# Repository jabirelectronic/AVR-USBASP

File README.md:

# USBasp - USB programmer for Atmel AVR controllers
The above programmer is from the website https://www.fischl.de/usbasp/
Modeled and redesigned.
There are some tips about this design:
Internal and external voltage separator section is considered.
A logic 5V output is provided.
A 3.3V output is also provided for low power micros.
And a 500 mA fuse is placed in this circuit to prevent short circuit and damage to the usb port.
The board is designed in two layers.
Be sure to use version 7 of kicad software to view the schematic and PCB map.

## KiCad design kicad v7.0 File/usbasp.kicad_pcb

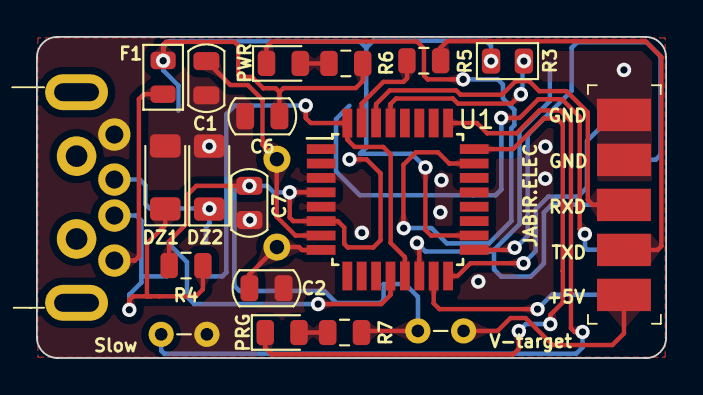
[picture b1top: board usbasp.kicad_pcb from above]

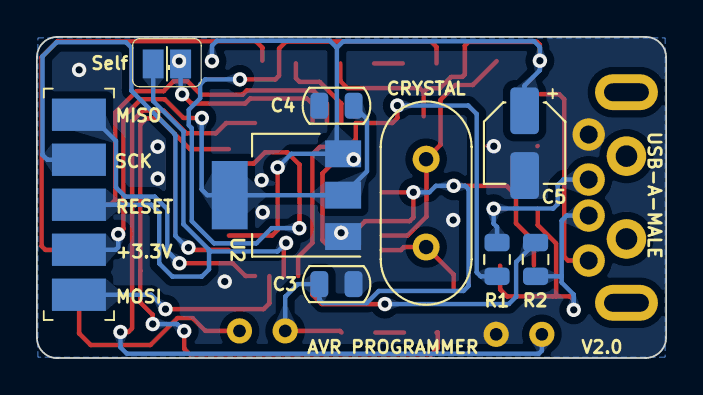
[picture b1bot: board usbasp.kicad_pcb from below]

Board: 2 copper layers, 35.0 x 17.8 mm, 28 parts (9 on the bottom side), 24 nets.

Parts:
+5V: B5B-XH-A_LF__SN_; PinHeader_1x5_P2.5mm_Drill1.1mm
C1, C2, C3, C4, C6, C7: 100nF_0603_16V; C_0805_2012Metric
C5: CP_Radial_D8.0mm_P5.00mm 4.7; CP_Elec_4x5.4
CRYSTAL: 16MHz_18pF_FA238; Crystal_HC49-U_Vertical
DZ1, DZ2: D3Z6V2BF; D_MiniMELF
F1: Fuse; Fuse_0805_2012Metric
MISO: B5B-XH-A_LF__SN_; PinHeader_1x5_P2.5mm_Drill1.1mm
PRG: LED; LED_0805_2012Metric
PWR: LED; LED_0805_2012Metric
R1, R2, R4, R5, R6, R7: 0R_0603; R_0805_2012Metric
R3: 110k_0603; R_0805_2012Metric
Self: Jumper_2_Bridged; JUMPER_SMD_1x2
Slow: Jumper_2_Bridged; Jumper_P2.54mm_D0.7mm
U1: ATmega8A-A; TQFP-32_7x7mm_P0.8mm
U2: AMS1117; SOT-223-3_TabPin2
USB-A-MALE: USB_A; USB_Male_A_UP2-AH-1-TH
V-target: Jumper_2_Bridged; Jumper_P2.54mm_D0.7mm

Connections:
Earth: +5V.4, +5V.5, C1.1, C2.1, C3.2, C4.1, C5.2, C6.2, C7.2, DZ1.2 (A), DZ2.2 (A), Slow.2 (B), U1.3 (GND), U1.5 (GND), U1.21 (AGND), U2.1 (ADJ), USB-A-MALE.4 (GND)
unnamed: DZ1.1 (K), R2.2, R4.1, USB-A-MALE.2 (D-)
unnamed: DZ2.1 (K), R1.2, USB-A-MALE.3 (D+)
unnamed: +5V.2, R5.2
unnamed: F1.2, USB-A-MALE.1 (VBUS)
unnamed: PWR.2 (A), R6.1
unnamed: PWR.1 (K), U1.23 (PC0)
unnamed: PRG.2 (A), R7.1
unnamed: PRG.1 (K), U1.24 (PC1)
unnamed: MISO.3, Self.1 (A), U1.14 (PB2)
unnamed: R3.2, Self.2 (B), U1.29 (PC6/~RESET)
unnamed: C3.1, C5.1, C6.1, C7.1, F1.1, R3.1, R4.2, R6.2, R7.2, U1.4 (VCC), U1.6 (VCC), U1.18 (AVCC), U2.3 (VI), V-target.1 (A)
unnamed: +5V.1, V-target.2 (B)
unnamed: R2.1, U1.12 (PB0)
unnamed: R1.1, U1.13 (PB1), U1.32 (PD2)
unnamed: MISO.5, U1.15 (PB3)
unnamed: MISO.1, U1.16 (PB4)
unnamed: MISO.2, U1.17 (PB5)
unnamed: C1.2, CRYSTAL.1, U1.7 (PB6/XTAL1)
unnamed: C2.2, CRYSTAL.2, U1.8 (PB7/XTAL2)
unnamed: +5V.3, U1.30 (PD0)
unnamed: R5.1, U1.31 (PD1)
unnamed: C4.2, MISO.4, U2.2 (VO)
SLOW: Slow.1 (A), U1.25 (PC2)

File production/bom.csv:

Designator,Footprint,Quantity,Value,LCSC Part #
"+5V, MISO",PinHeader_1x5_P2.5mm_Drill1.1mm,2,B5B-XH-A_LF__SN_,B5B-XH-A(LF)(SN)
C1,0805,1,100nF_0603_16V,
C2,0805,1,100nF_0603_16V,
C3,0805,1,100nF_0603_16V,
C4,0805,1,100nF_0603_16V,
C5,CP_Elec_4x5.4,1,CP_Radial_D8.0mm_P5.00mm 4.7,
C6,0805,1,100nF_0603_16V,
C7,0805,1,100nF_0603_16V,
CRYSTAL,Crystal_HC49-U_Vertical,1,16MHz_18pF_FA238,
"DZ1, DZ2",D_MiniMELF,2,D3Z6V2BF,
F1,0805,1,Fuse,
PRG,0805,1,LED,
PWR,0805,1,LED,
R1,0805,1,0R_0603,
R2,0805,1,0R_0603,
R3,0805,1,110k_0603,
R4,0805,1,0R_0603,
R5,0805,1,0R_0603,
R6,0805,1,0R_0603,
R7,0805,1,0R_0603,
Self,JUMPER_SMD_1x2,1,Jumper_2_Bridged,
"Slow, V-target",Jumper_P2.54mm_D0.7mm,2,Jumper_2_Bridged,
U1,TQFP-32_7x7mm_P0.8mm,1,ATmega8A-A,
U2,SOT-223-3_TabPin2,1,AMS1117,
USB-A-MALE,USB_Male_A_UP2-AH-1-TH,1,USB_A,
